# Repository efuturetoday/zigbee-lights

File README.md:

JN-AN-1171-ZigBee-LightLink-Demo

Copyright NXP B.V. 2012. All rights reserved

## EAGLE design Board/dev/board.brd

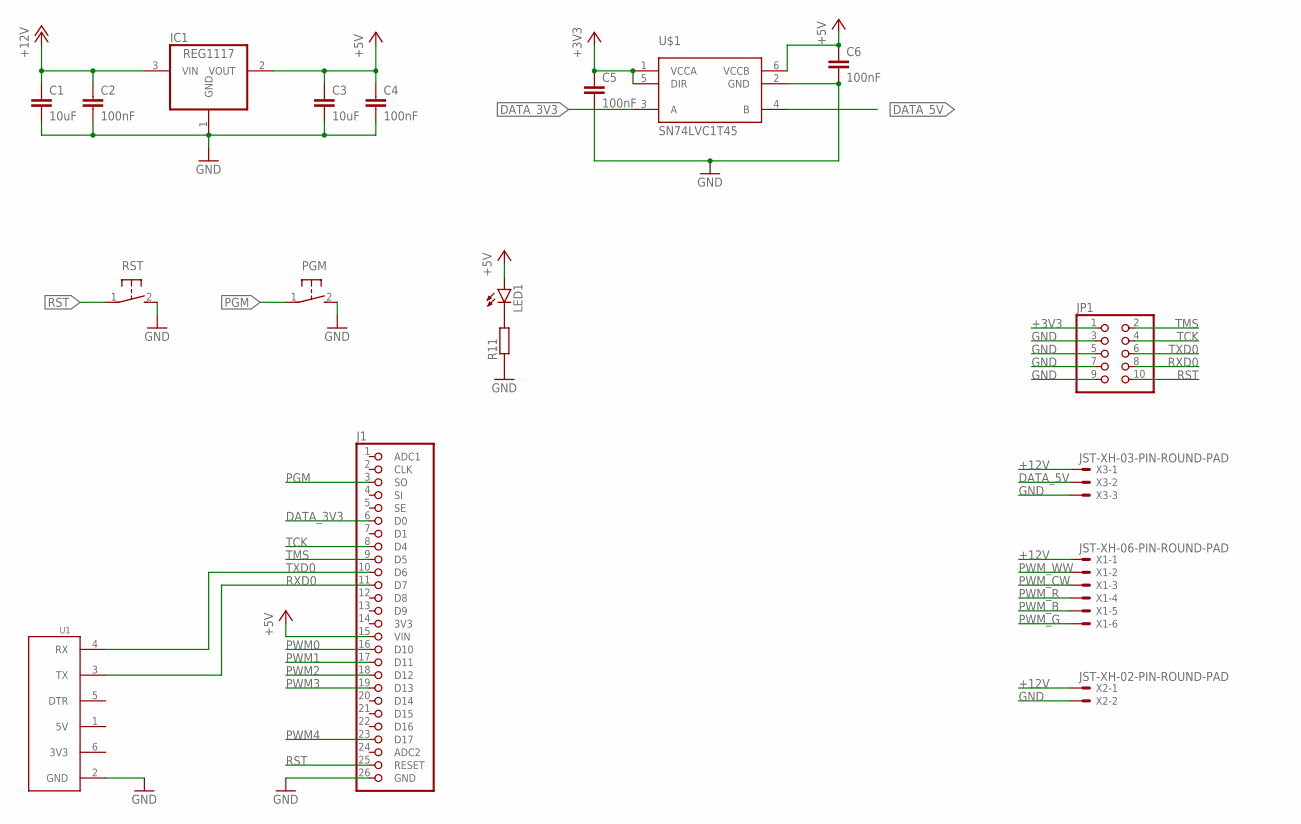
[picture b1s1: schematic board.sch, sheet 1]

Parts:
C1, C3: 10uF; C0603
C2, C4, C5, C6: 100nF; C0603
IC1: REG1117; SOT223
J1: E75-2G4M20S-SOCKET
JP1: PINHD-2X5; 2X05
LED1: LEDCHIP-LED0603; CHIP-LED0603
PGM: BUTTON3X4
R11: R-EU_R0603; R0603
RST: BUTTON3X4
U1: CP2102-BOARD
U$1: SN74LVC1T45; SOT23-6
X1: JST-XH-06-PIN-ROUND-PAD; JST-XH-06-PACKAGE-ROUND-PAD
X2: JST-XH-02-PIN-ROUND-PAD; JST-XH-02-PACKAGE-ROUND-PAD
X3: JST-XH-03-PIN-ROUND-PAD; JST-XH-03-PACKAGE-ROUND-PAD

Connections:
+3V3: C5.1, JP1.1, U$1.1 (VCCA), U$1.5 (DIR)
+5V: C3.1, C4.1, C6.1, IC1.2 (VOUT), J1.15 (VIN), LED1.A, U$1.6 (VCCB)
+12V: C1.1, C2.1, IC1.3 (VIN), X1.1, X2.1, X3.1
DATA_3V3: J1.6 (D0), U$1.3 (A)
DATA_5V: U$1.4 (B), X3.2
GND: C1.2, C2.2, C3.2, C4.2, C5.2, C6.2, IC1.1 (GND), J1.26 (GND), JP1.3, JP1.5, JP1.7, JP1.9, PGM.2 (S), R11.1, RST.2 (S), U1.2 (GND), U$1.2 (GND), X2.2, X3.3; also elsewhere on the board
unnamed: LED1.C, R11.2
PGM: J1.3 (SO), PGM.1
PWM0: J1.16 (D10); also elsewhere on the board
PWM1: J1.17 (D11); also elsewhere on the board
PWM2: J1.18 (D12); also elsewhere on the board
PWM3: J1.19 (D13); also elsewhere on the board
PWM4: J1.23 (D17); also elsewhere on the board
PWM_B: X1.5; also elsewhere on the board
PWM_CW: X1.3; also elsewhere on the board
PWM_G: X1.6; also elsewhere on the board
PWM_R: X1.4; also elsewhere on the board
PWM_WW: X1.2; also elsewhere on the board
RST: J1.25 (RESET), JP1.10, RST.1
RXD0: J1.11 (D7), JP1.8, U1.3 (TX)
TCK: J1.8 (D4), JP1.4
TMS: J1.9 (D5), JP1.2
TXD0: J1.10 (D6), JP1.6, U1.4 (RX)

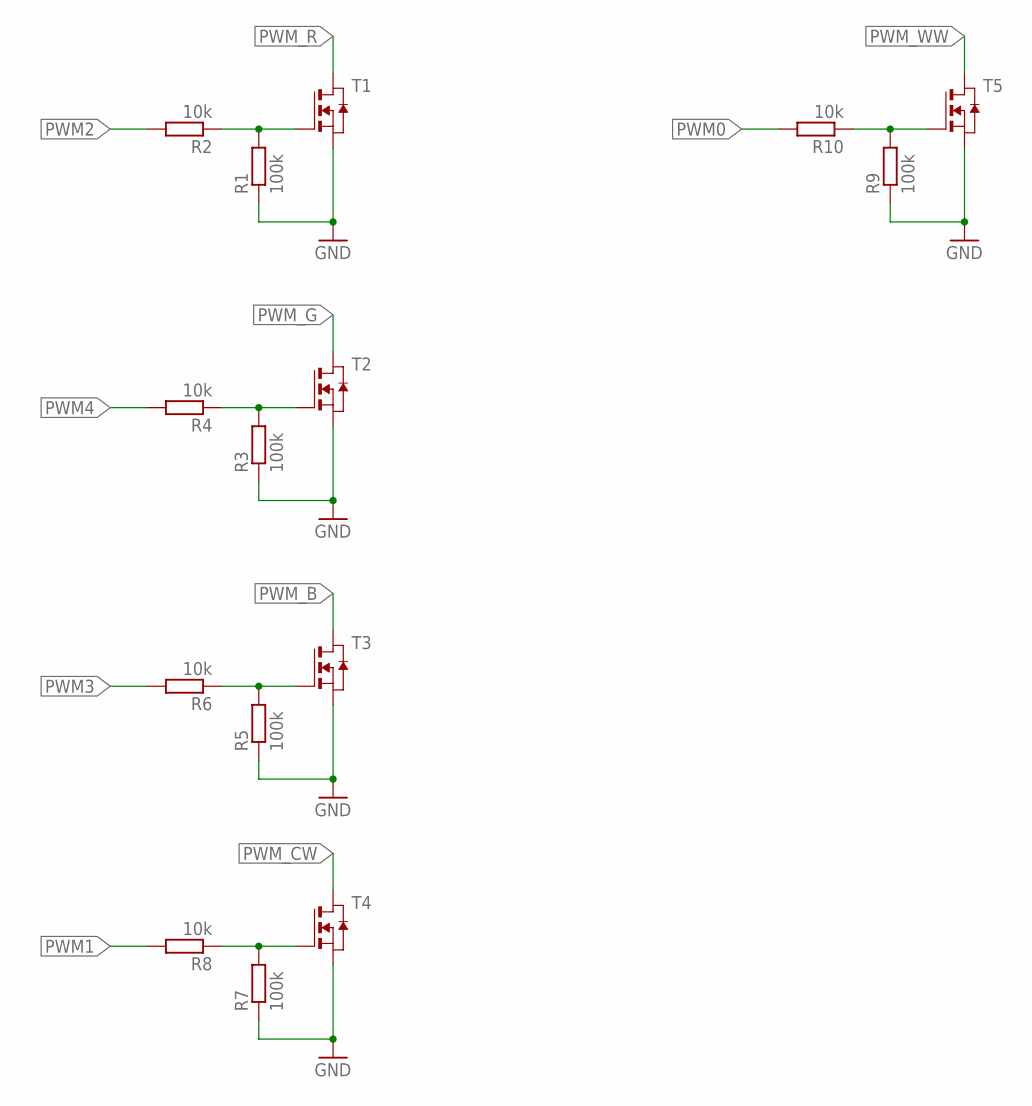
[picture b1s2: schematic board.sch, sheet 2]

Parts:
R1, R3, R5, R7, R9: 100k; R0603
R2, R4, R6, R8, R10: 10k; R0603
T1, T2, T3, T4, T5: NMOSSOT23; SOT-23

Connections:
GND: R1.1, R3.1, R5.1, R7.1, R9.1, T1.2 (S), T2.2 (S), T3.2 (S), T4.2 (S), T5.2 (S); also elsewhere on the board
unnamed: R1.2, R2.1, T1.3 (G)
unnamed: R3.2, R4.1, T2.3 (G)
unnamed: R5.2, R6.1, T3.3 (G)
unnamed: R7.2, R8.1, T4.3 (G)
unnamed: R9.2, R10.1, T5.3 (G)
PWM0: R10.2; also elsewhere on the board
PWM1: R8.2; also elsewhere on the board
PWM2: R2.2; also elsewhere on the board
PWM3: R6.2; also elsewhere on the board
PWM4: R4.2; also elsewhere on the board
PWM_B: T3.1 (D); also elsewhere on the board
PWM_CW: T4.1 (D); also elsewhere on the board
PWM_G: T2.1 (D); also elsewhere on the board
PWM_R: T1.1 (D); also elsewhere on the board
PWM_WW: T5.1 (D); also elsewhere on the board

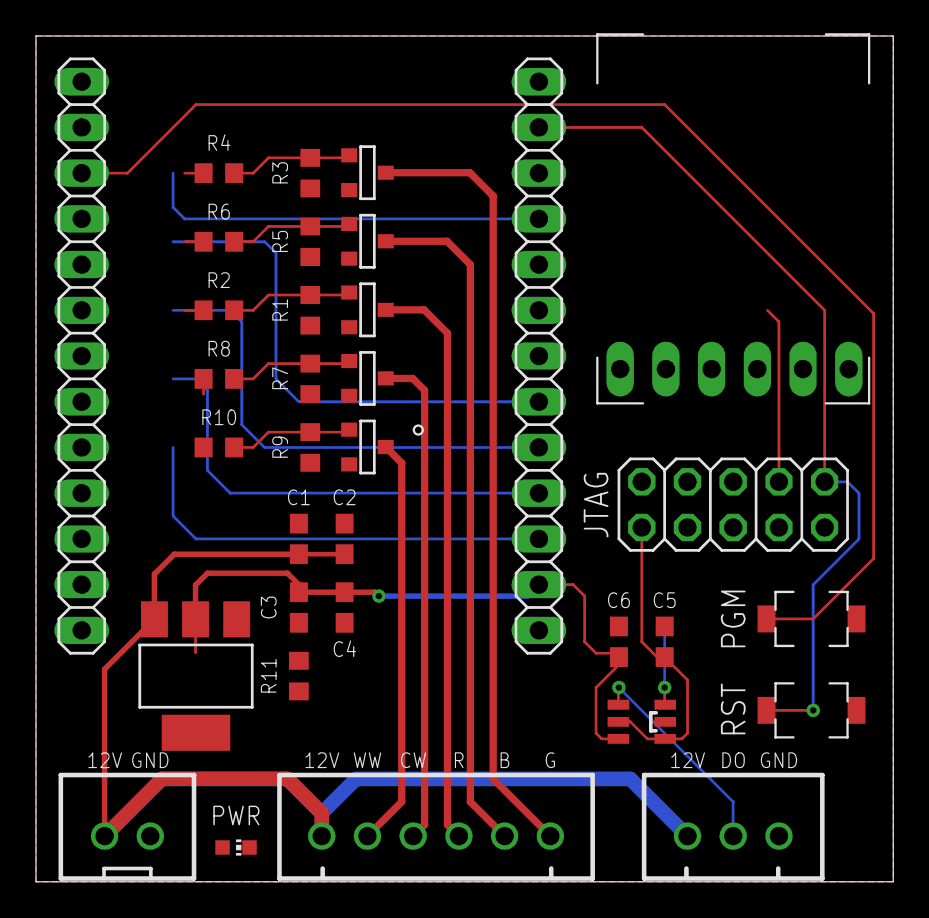
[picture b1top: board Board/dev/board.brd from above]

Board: 2 copper layers, 47.6 x 47.0 mm, 33 parts (0 on the bottom side), 28 nets.

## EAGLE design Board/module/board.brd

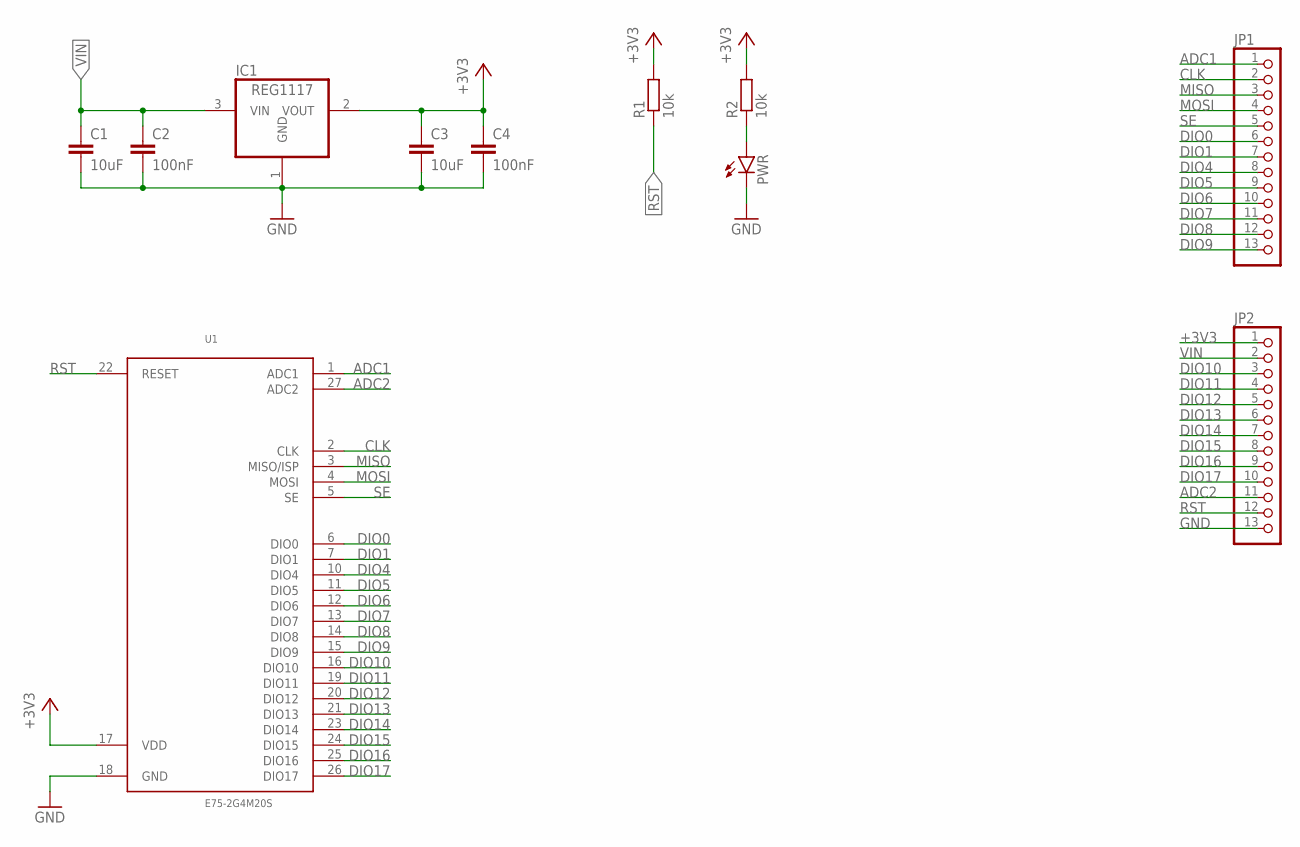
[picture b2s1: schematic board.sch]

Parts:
C1, C3: 10uF; C0603
C2, C4: 100nF; C0603
IC1: REG1117; SOT223
JP1, JP2: PINHD-1X13; 1X13
PWR: LEDSML0603; SML0603
R1, R2: 10k; R0603
U1: E75-2G4M20S

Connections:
+3V3: C3.1, C4.1, IC1.2 (VOUT), JP2.1, R1.2, R2.2, U1.17 (VDD)
ADC1: JP1.1, U1.1 (ADC1)
ADC2: JP2.11, U1.27 (ADC2)
CLK: JP1.2, U1.2 (CLK)
DIO0: JP1.6, U1.6 (DIO0)
DIO1: JP1.7, U1.7 (DIO1)
DIO4: JP1.8, U1.10 (DIO4)
DIO5: JP1.9, U1.11 (DIO5)
DIO6: JP1.10, U1.12 (DIO6)
DIO7: JP1.11, U1.13 (DIO7)
DIO8: JP1.12, U1.14 (DIO8)
DIO9: JP1.13, U1.15 (DIO9)
DIO10: JP2.3, U1.16 (DIO10)
DIO11: JP2.4, U1.19 (DIO11)
DIO12: JP2.5, U1.20 (DIO12)
DIO13: JP2.6, U1.21 (DIO13)
DIO14: JP2.7, U1.23 (DIO14)
DIO15: JP2.8, U1.24 (DIO15)
DIO16: JP2.9, U1.25 (DIO16)
DIO17: JP2.10, U1.26 (DIO17)
GND: C1.2, C2.2, C3.2, C4.2, IC1.1 (GND), JP2.13, PWR.C, U1.18 (GND)
MISO: JP1.3, U1.3 (MISO/ISP)
MOSI: JP1.4, U1.4 (MOSI)
unnamed: PWR.A, R2.1
RST: JP2.12, R1.1, U1.22 (RESET)
SE: JP1.5, U1.5 (SE)
VIN: C1.1, C2.1, IC1.3 (VIN), JP2.2

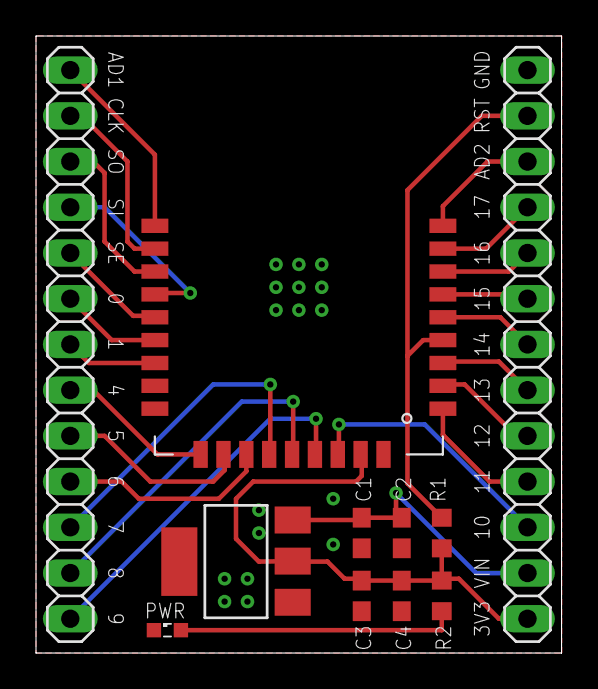
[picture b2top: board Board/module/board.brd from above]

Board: 2 copper layers, 29.2 x 34.3 mm, 11 parts (0 on the bottom side), 27 nets.

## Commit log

2020-01-04 chore: added initial project
2020-01-04 docs: added copyright
2020-01-09 initial
